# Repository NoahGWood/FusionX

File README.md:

# FusionX
FusionX is an open-source, open-hardware smartphone

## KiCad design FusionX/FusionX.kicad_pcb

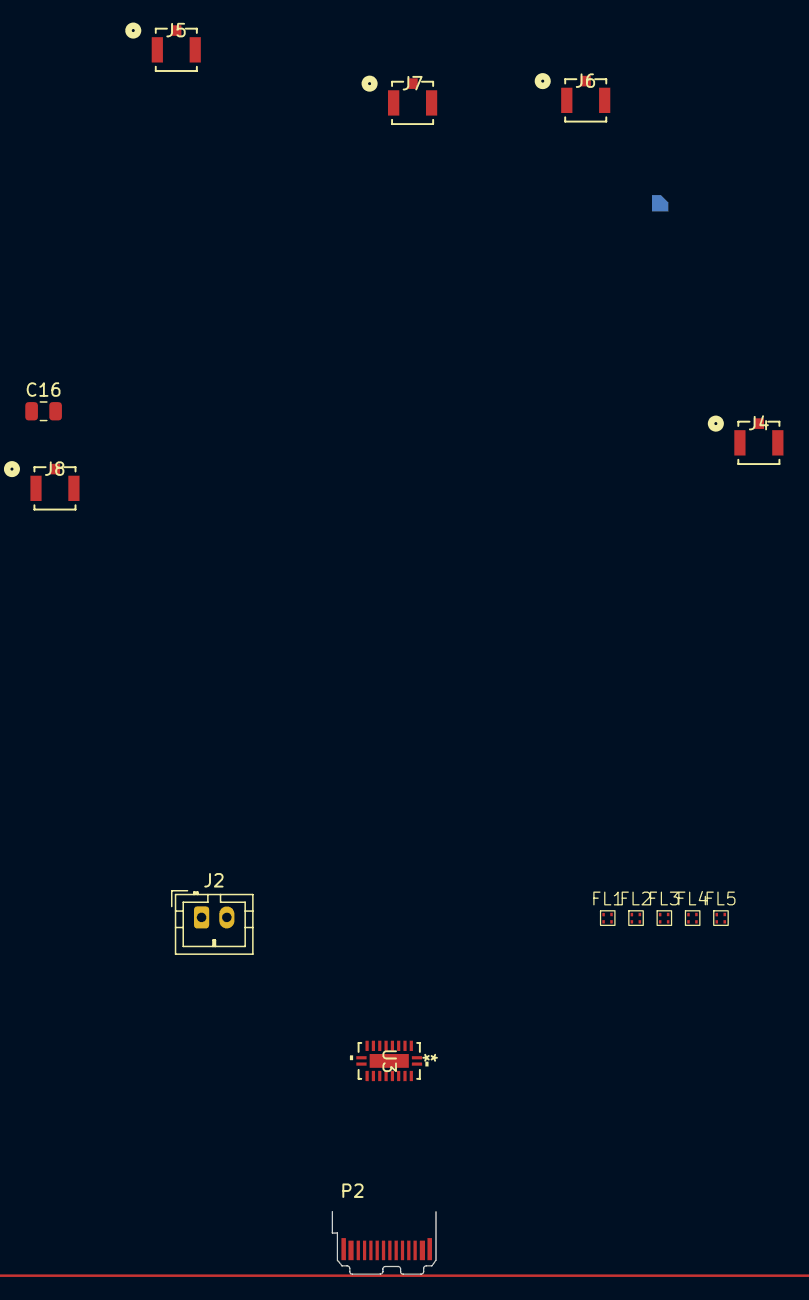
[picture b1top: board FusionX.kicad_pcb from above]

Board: 2 copper layers, 15 parts (1 on the bottom side), 22 nets, no tracks yet.

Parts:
C16: 100pF; C_0805_2012Metric
FL1, FL2, FL3, FL4, FL5: C167454; DLP0SN900HL2L
J2: BAT; JST_PH_B2B-PH-K_1x02_P2.00mm_Vertical
J4: Main; CONN_U.FL-R-SMT-110_HIR
J5: DRX; CONN_U.FL-R-SMT-110_HIR
J6: WIFI; CONN_U.FL-R-SMT-110_HIR
J7: FM; CONN_U.FL-R-SMT-110_HIR
J8: GPS; CONN_U.FL-R-SMT-110_HIR
P2: USB_C_Plug; USB_C_Plug_JAE_DX07P024AJ1
U1: SC600YNAPA-E53-UGADA; SC600Y-SC600T_QWS
U3: PI3USB302-AZBEX; 20TQFN-ZB_PI3USB302-A_DIO

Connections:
+3.3V: U3.1 (VDD), U3.6 (VDD), U3.10 (VDD)
-BATT: J2.2, P2.A1 (GND), P2.A12 (GND), P2.B1 (GND), P2.B12 (GND), P2.S1 (SHIELD), U1.3 (GND), U1.4 (GND), U1.18 (GND), U1.20 (GND), U1.28 (BAT_MINUS), U1.31 (GND), U1.34 (GND), U1.35 (GND), U1.40 (GND), U1.43 (GND), U1.47 (GND), U1.56 (GND), U1.62 (GND), U1.87 (GND), U1.112 (GND), U1.125 (GND), U1.128 (GND), U1.130 (GND), U1.133 (GND), U1.135 (GND), U1.148 (GND), U1.150 (GND), U1.159 (GND), U1.163 (GND), U1.170 (GND), U1.173 (GND), U1.176 (GND), U1.182 (GND), U1.193 (GND), U1.195 (GND), U1.219 (GND), U1.225 (GND), U1.243 (GND), U1.257 (GND), U1.258 (GND), U1.259 (GND), U1.260 (GND), U1.261 (GND), U1.262 (GND), U1.263 (GND), U1.264 (GND), U1.265 (GND), U1.266 (GND), U1.267 (GND), U1.268 (GND), U1.269 (GND), U1.270 (GND), U1.271 (GND), U1.272 (GND), U1.273 (GND), U1.274 (GND), U1.275 (GND), U1.276 (GND), U1.277 (GND), U1.278 (GND), U1.279 (GND), U1.280 (GND), U1.281 (GND), U1.282 (GND), U1.283 (GND), U1.284 (GND), U1.285 (GND), U1.286 (GND), U1.287 (GND), U1.288 (GND), U1.289 (GND), U1.290 (GND), U1.291 (GND), U1.292 (GND), U1.293 (GND), U1.294 (GND), U1.295 (GND), U1.296 (GND), U1.297 (GND), U1.298 (GND), U1.299 (GND), U1.300 (GND), U1.301 (GND), U1.302 (GND), U1.303 (GND), U1.304 (GND), U1.305 (GND), U1.306 (GND), U1.307 (GND), U1.308 (GND), U1.309 (GND), U1.310 (GND), U1.311 (GND), U1.312 (GND), U1.313 (GND), U1.314 (GND), U1.315 (GND), U1.316 (GND), U1.317 (GND), U1.318 (GND), U1.319 (GND), U1.320 (GND), U1.321 (GND), U1.322 (GND), U1.323 (GND), U3.5 (GND), U3.11 (GND), U3.20 (GND), U3.21 (GND)
unnamed: C16.2, J8.1
unnamed: P2.B11 (RX1+), U3.17 (RX1+)
unnamed: P2.B10 (RX1-), U3.16 (RX1-)
unnamed: P2.A11 (RX2+), U3.13 (RX2+)
unnamed: P2.A10 (RX2-), U3.12 (RX2-)
unnamed: P2.A2 (TX1+), U3.19 (TX1+)
unnamed: P2.A3 (TX1-), U3.18 (TX1-)
unnamed: P2.B2 (TX2+), U3.15 (TX2+)
unnamed: P2.B3 (TX2-), U3.14 (TX2-)
USB_CC1: P2.A5 (CC), U1.224 (USBC_CC1)
USB_CC2: P2.B5 (VCONN), U1.223 (USBC_CC2)
USB_DM: P2.A7 (D-), U1.33 (USB_DM)
USB_DP: P2.A6 (D+), U1.32 (USB_DP)
USB_SS_RX_M: U1.172 (USB_SS_RX_M), U3.8 (RX-)
USB_SS_RX_P: U1.171 (USB_SS_RX_P), U3.7 (RX+)
USB_SS_SEL: U1.226 (USB_SS_SEL), U3.9 (SEL)
USB_SS_TX_M: U1.175 (USB_SS_TX__M), U3.4 (TX-)
USB_SS_TX_P: U1.174 (USB_SS_TX__P), U3.3 (TX+)
VBAT: U1.27 (BAT_PLUS), U1.36 (VBAT), U1.37 (VBAT), U1.38 (VBAT)
VBUS: P2.A4 (VBUS), P2.A9 (VBUS), P2.B4 (VBUS), P2.B9 (VBUS)

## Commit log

2023-08-15 Initial commit. Added Raspi-compatible LCD connector, started battery & USB
2023-08-15 Updated sheet
2023-08-15 Finished RaspiLCD Added Antennas Started secondary LCD
2023-08-18 Implemented: USB-C Super Speed Capacitve Touch Screen Secondary LCD
    Started On:
    PCB Layout
    Case Design
2023-08-18 Removed unneeded files

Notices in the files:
FusionX/FusionX.kicad_pcb:
License: The Unlicense
